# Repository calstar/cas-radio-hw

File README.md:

View this project on [CADLAB.io](https://cadlab.io/project/23053). 

# cas-radio-hw
Common Avionics Stack - Radio Module - Hardware

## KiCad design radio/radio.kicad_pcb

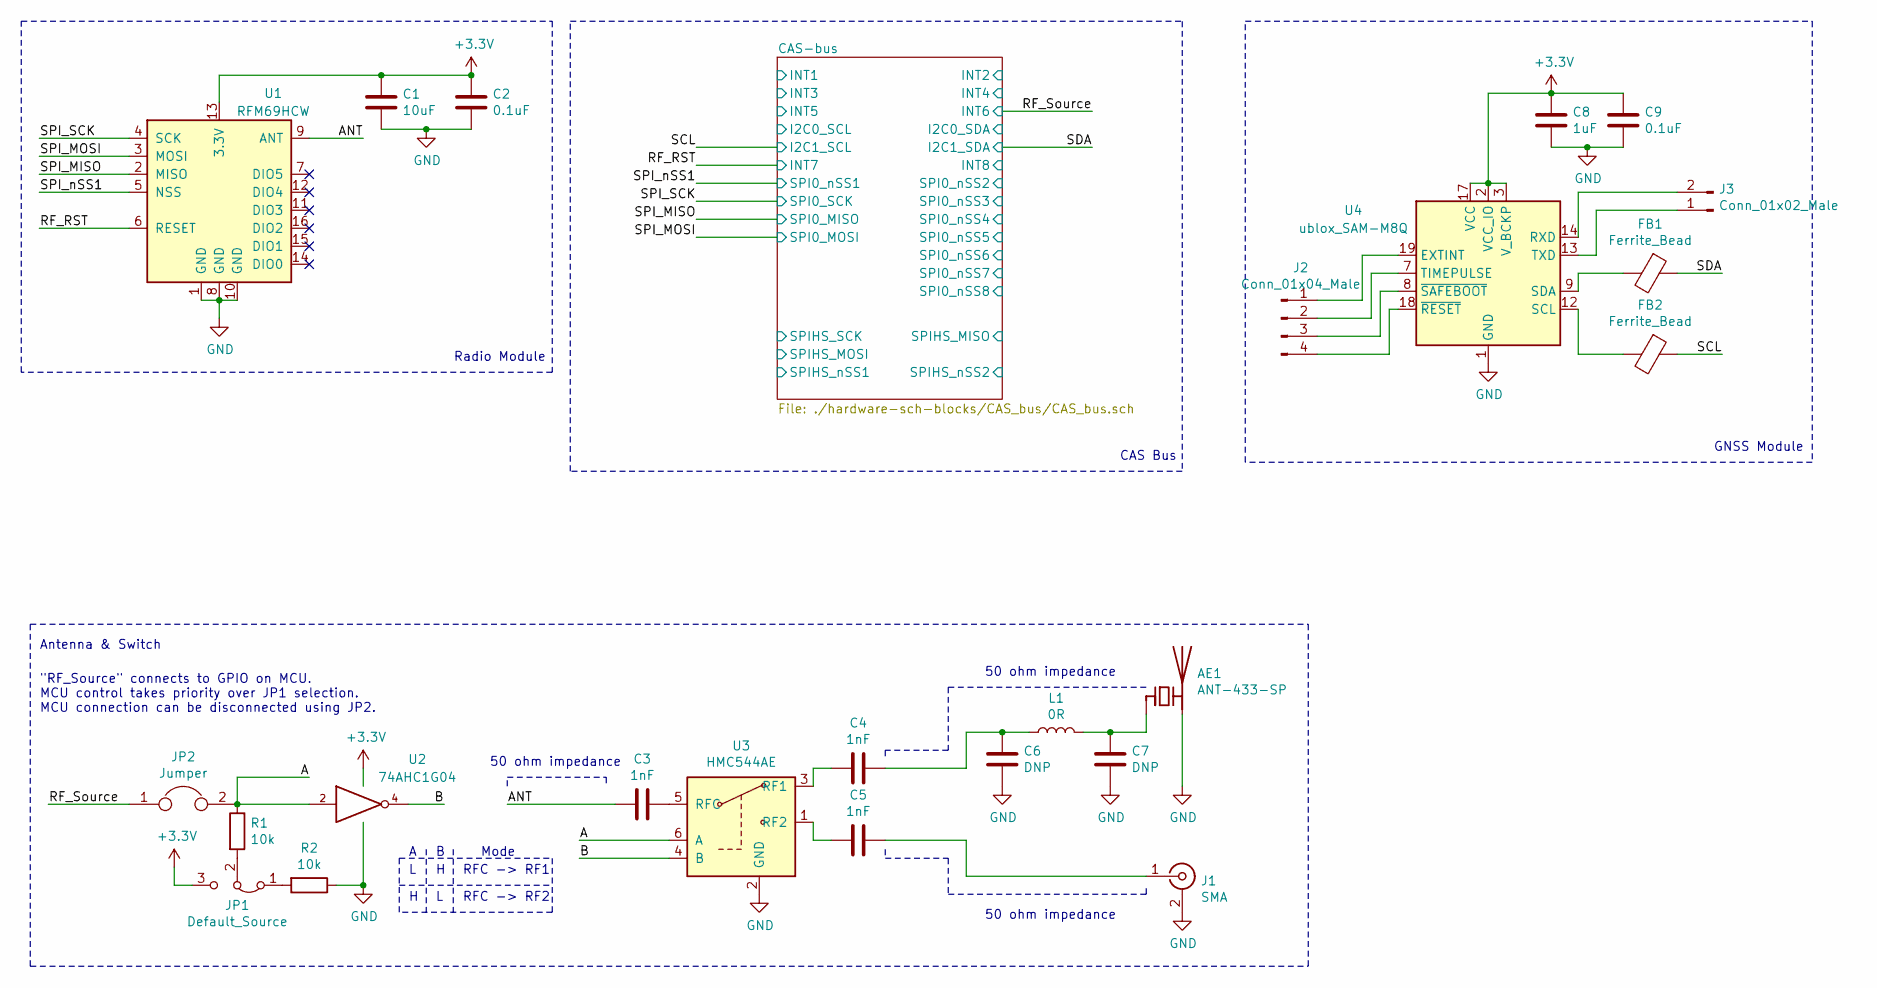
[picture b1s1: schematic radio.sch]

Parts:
AE1: ANT-433-SP
C1: 10uF; C_0603_1608Metric
C2, C9: 0.1uF; C_0603_1608Metric
C3, C4, C5: 1nF; C_0603_1608Metric
C6, C7: DNP; C_0603_1608Metric
C8: 1uF; C_0603_1608Metric
FB1, FB2: Ferrite_Bead; L_0603_1608Metric
J1: SMA; SMA_Molex_73391-0083_Horizontal
J2: Conn_01x04_Male; PinHeader_1x04_P2.54mm_Vertical_SMD_Pin1Left
J3: Conn_01x02_Male; PinHeader_1x02_P2.54mm_Vertical_SMD_Pin1Left
JP1: Default_Source; SolderJumper-3_P1.3mm_Bridged12_RoundedPad1.0x1.5mm
JP2: Jumper; SolderJumper-2_P1.3mm_Bridged_RoundedPad1.0x1.5mm
L1: 0R; L_0603_1608Metric
R1, R2: 10k; R_0603_1608Metric
U1: RFM69HCW; RFM69HCW-XXXS2
U2: 74AHC1G04; SOT-353_SC-70-5
U3: HMC544AE; SOT-23-6
U4: ublox_SAM-M8Q

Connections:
+3V3: C1.1, C2.1, C8.1, C9.1, JP1.3 (B), U1.13 (3.3V), U2.5 (VCC), U4.2 (VCC_IO), U4.3 (V_BCKP), U4.17 (VCC); also elsewhere on the board
/A: JP2.2, R1.1, U2.2, U3.6 (A)
/ANT: C3.2, U1.9 (ANT)
/B: U2.4, U3.4 (B)
/RF_RST: U1.6 (RESET); also elsewhere on the board
/RF_Source: JP2.1; also elsewhere on the board
/SCL: FB2.1; also elsewhere on the board
/SDA: FB1.1; also elsewhere on the board
/SPI_MISO: U1.2 (MISO); also elsewhere on the board
/SPI_MOSI: U1.3 (MOSI); also elsewhere on the board
/SPI_SCK: U1.4 (SCK); also elsewhere on the board
/SPI_nSS1: U1.5 (NSS); also elsewhere on the board
GND: AE1.2 (PCB_Trace), C1.2, C2.2, C6.2, C7.2, C8.2, C9.2, J1.2 (Ext), R2.1, U1.1 (GND), U1.8 (GND), U1.10 (GND), U2.3 (GND), U3.2 (GND), U4.1 (GND), U4.4 (GND), U4.5 (GND), U4.6 (GND), U4.10 (GND), U4.11 (GND), U4.15 (GND), U4.16 (GND), U4.20 (GND); also elsewhere on the board
unnamed: AE1.1 (FEED), C7.1, L1.2
unnamed: C3.1, U3.5 (RFC)
unnamed: C4.1, C6.1, L1.1
unnamed: C4.2, U3.3 (RF1)
unnamed: C5.1, J1.1 (In)
unnamed: C5.2, U3.1 (RF2)
unnamed: FB1.2, U4.9 (SDA)
unnamed: FB2.2, U4.12 (SCL)
unnamed: J2.1, U4.19 (EXTINT)
unnamed: J2.2, U4.7 (TIMEPULSE)
unnamed: J2.3, U4.8 (~SAFEBOOT)
unnamed: J2.4, U4.18 (~RESET)
unnamed: J3.1, U4.13 (TXD)
unnamed: J3.2, U4.14 (RXD)
unnamed: JP1.1 (A), R2.2
unnamed: JP1.2 (C), R1.2

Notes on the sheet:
CAS Bus
50 ohm impedance
RFC -> RF1
RFC -> RF2
Mode
Radio Module
Antenna & Switch
"RF_Source" connects to GPIO on MCU. MCU control takes priority over JP1 selection. MCU connection can be disconnected using JP2.
GNSS Module

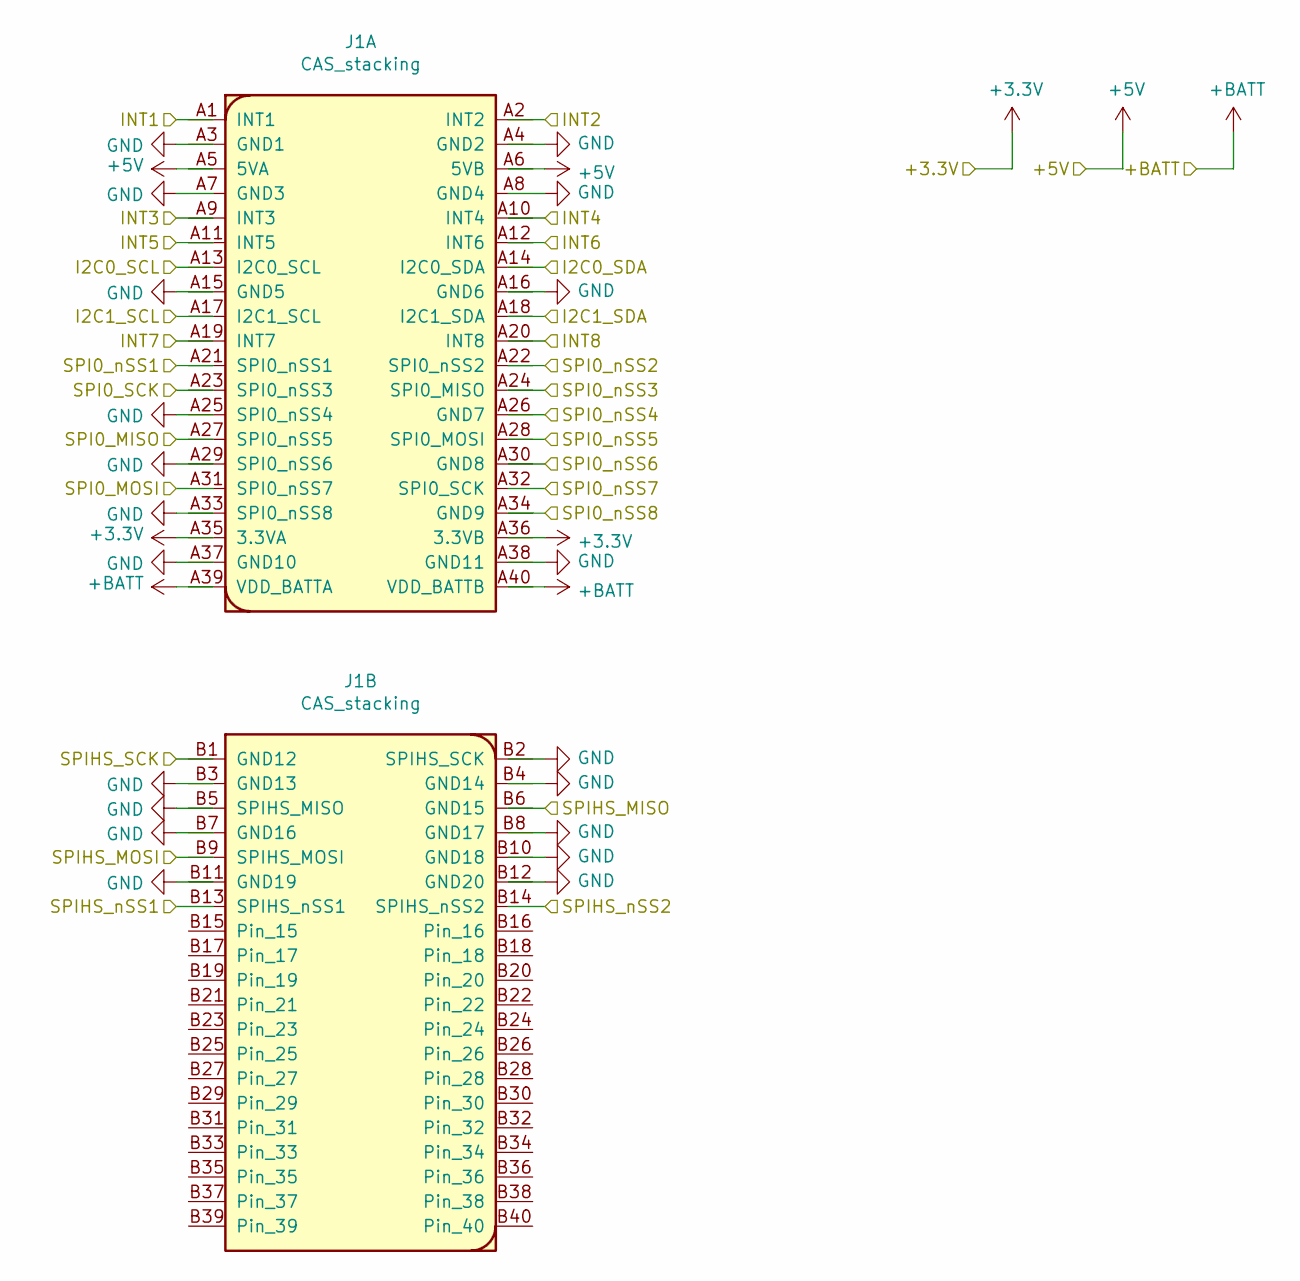
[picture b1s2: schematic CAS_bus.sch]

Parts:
J1: CAS_stacking; CAS_physical

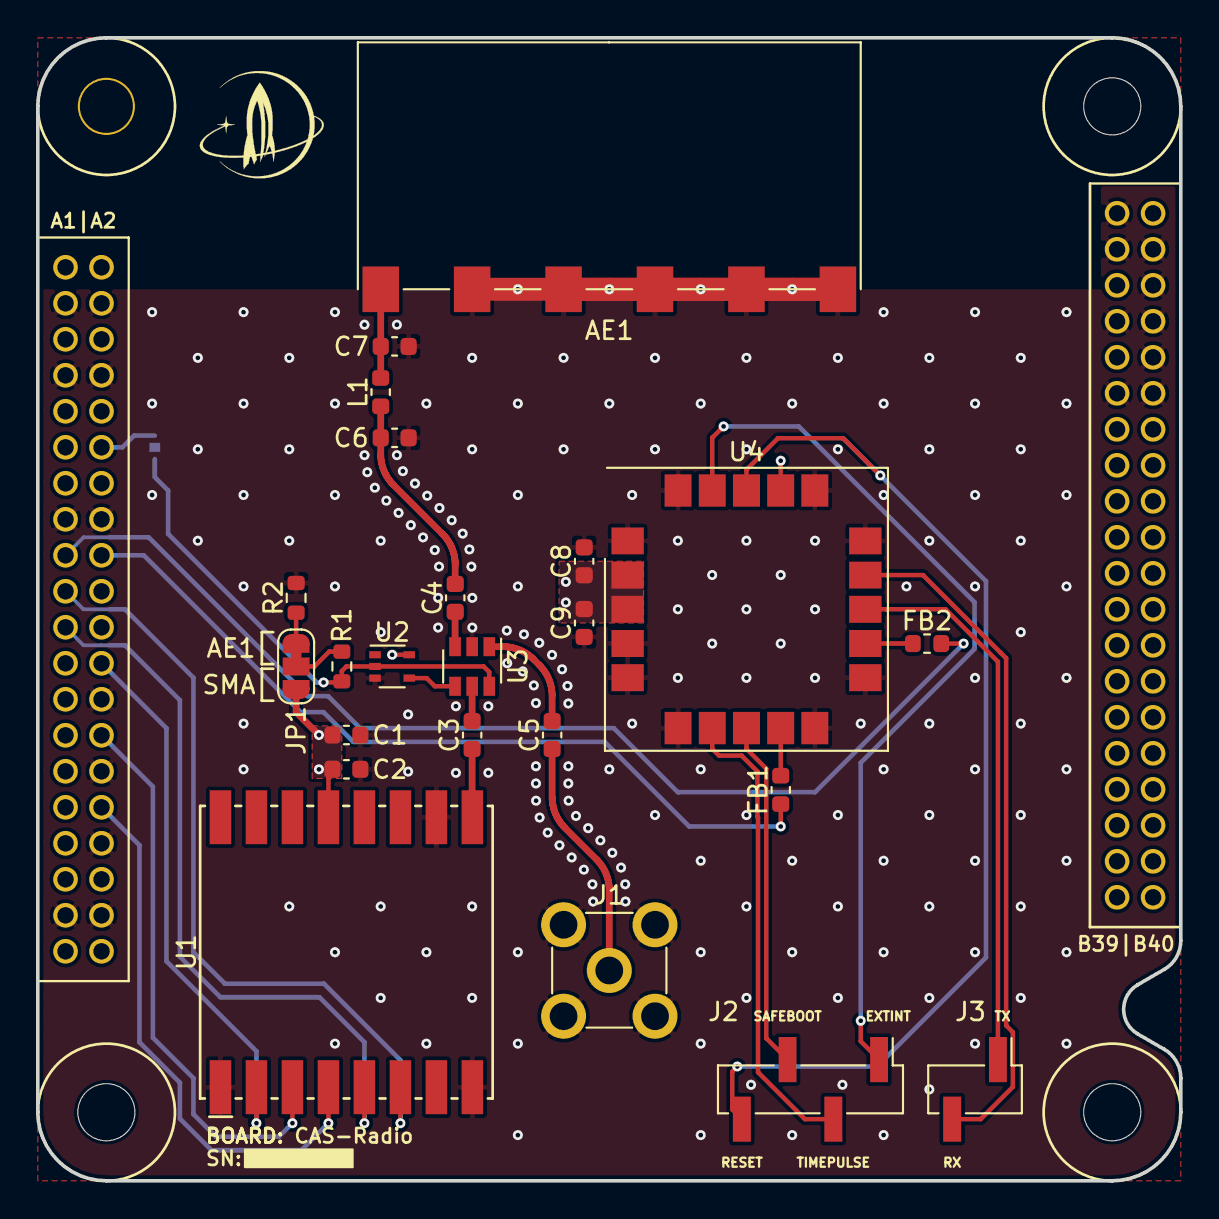
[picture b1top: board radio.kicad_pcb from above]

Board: 4 copper layers, 63.5 x 63.5 mm, 25 parts (1 on the bottom side), 31 nets.

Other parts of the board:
J1001: CAS_stacking; CAS_physical

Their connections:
+3V3: J1001.A35, J1001.A36; also elsewhere on the board
+5V: J1001.A5, J1001.A6
+BATT: J1001.A39, J1001.A40
/RF_RST: J1001.A19; also elsewhere on the board
/RF_Source: J1001.A12; also elsewhere on the board
/SCL: J1001.A17; also elsewhere on the board
/SDA: J1001.A18; also elsewhere on the board
/SPI_MISO: J1001.A24; also elsewhere on the board
/SPI_MOSI: J1001.A28; also elsewhere on the board
/SPI_SCK: J1001.A32; also elsewhere on the board
/SPI_nSS1: J1001.A21; also elsewhere on the board
GND: J1001.A3, J1001.A4, J1001.A7, J1001.A8, J1001.A15, J1001.A16, J1001.A26, J1001.A30, J1001.A34, J1001.A37, J1001.A38, J1001.B1, J1001.B3, J1001.B4, J1001.B6, J1001.B7, J1001.B8, J1001.B10, J1001.B11, J1001.B12; also elsewhere on the board

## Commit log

2020-06-27 Backlink to CADLAB.io has been added.
2020-08-22 init
2020-11-03 Attempting to push recent radio update
2020-11-08 clain up depth
2020-11-08 add submodule
2020-11-08 updated footprints
2020-11-08 gitmodules
2020-11-12 moving to outer folder
2021-01-03 4-layer radio board
2021-01-09 Added solder jumper to select source, removed radio INT
2021-01-09 tweaked traces
2021-01-12 Add test pins
2021-01-15 moved logo to silkscreen, shifted over debug connector for gps and added silkscreen
2021-02-07 Added digikey part numbers
